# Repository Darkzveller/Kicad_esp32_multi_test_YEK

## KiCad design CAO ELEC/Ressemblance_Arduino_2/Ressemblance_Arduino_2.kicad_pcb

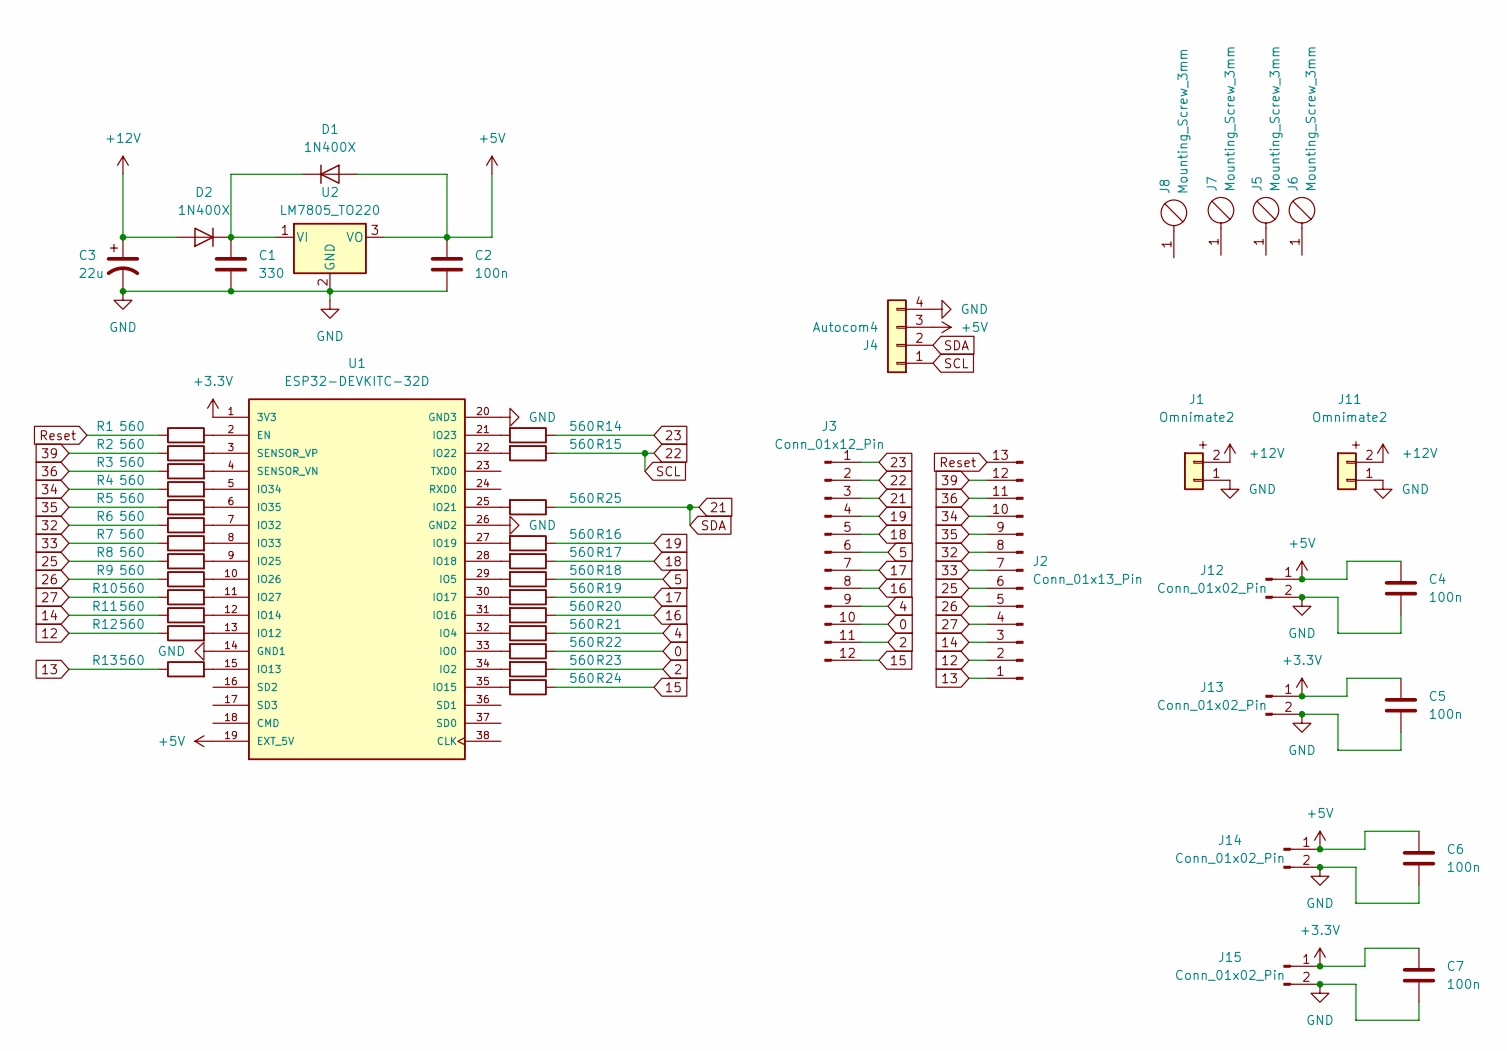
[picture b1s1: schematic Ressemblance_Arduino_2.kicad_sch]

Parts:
C1: 330; C_Rect_L7.0mm_W2.5mm_P5.00mm
C2, C4, C5, C6, C7: 100n; C_Rect_L7.0mm_W2.5mm_P5.00mm
C3: 22u; CP_Radial_D5.0mm_P2.50mm
D1, D2: 1N400X; D_DO-41_SOD81_P10.16mm_Horizontal
J1, J11: Omnimate2; OmnimateSL-5,08_1x02_P5.08mm_Vertical
J2: Conn_01x13_Pin; PinHeader_1x13_P2.54mm_Vertical
J3: Conn_01x12_Pin; PinHeader_1x12_P2.54mm_Vertical
J4: Autocom4; PinHeader_1x04_P2.00mm_Vertical
J5, J6, J7, J8: Mounting_Screw_3mm
J12, J13, J14, J15: Conn_01x02_Pin; PinHeader_1x02_P2.54mm_Vertical
R1, R2, R3, R4, R5, R6, R7, R8, R9, R10, R11, R12, R13, R14, R15, R16, R17, R18, R19, R20, R21, R22, R23, R24, R25: 560; R_Axial_DIN0207_L6.3mm_D2.5mm_P10.16mm_Horizontal
U1: ESP32-DEVKITC-32D; MODULE_ESP32-DEVKITC-32D; PARTREV 4
U2: LM7805_TO220; TO-220-3_Horizontal_TabDown

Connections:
0: J3.10, R22.1
2: J3.11, R23.1
4: J3.9, R21.1
5: J3.6, R18.1
12: J2.2, R12.1
13: J2.1, R13.1
14: J2.3, R11.1
15: J3.12, R24.1
16: J3.8, R20.1
17: J3.7, R19.1
18: J3.5, R17.1
19: J3.4, R16.1
21: J3.3, J4.2, R25.1
22: J3.2, J4.1, R15.1
23: J3.1, R14.1
25: J2.6, R8.1
26: J2.5, R9.1
27: J2.4, R10.1
32: J2.8, R6.1
33: J2.7, R7.1
34: J2.10, R4.1
35: J2.9, R5.1
36: J2.11, R3.1
39: J2.12, R2.1
+3.3V: C5.1, C7.1, J13.1, J15.1, U1.1 (3V3)
+5V: C2.1, C4.1, C6.1, D1.2 (A), J4.3, J12.1, J14.1, U1.19 (EXT_5V), U2.3 (VO)
+12V: C3.1, D2.2 (A), J1.2, J11.2
GND: C1.2, C2.2, C3.2, C4.2, C5.2, C6.2, C7.2, J1.1, J4.4, J11.1, J12.2, J13.2, J14.2, J15.2, U1.14 (GND1), U1.20 (GND3), U1.26 (GND2), U2.2 (GND)
unnamed: C1.1, D1.1 (K), D2.1 (K), U2.1 (VI)
unnamed: R1.2, U1.2 (EN)
unnamed: R22.2, U1.33 (IO0)
unnamed: R23.2, U1.34 (IO2)
unnamed: R21.2, U1.32 (IO4)
unnamed: R18.2, U1.29 (IO5)
unnamed: R12.2, U1.13 (IO12)
unnamed: R13.2, U1.15 (IO13)
unnamed: R11.2, U1.12 (IO14)
unnamed: R24.2, U1.35 (IO15)
unnamed: R20.2, U1.31 (IO16)
unnamed: R19.2, U1.30 (IO17)
unnamed: R17.2, U1.28 (IO18)
unnamed: R16.2, U1.27 (IO19)
unnamed: R25.2, U1.25 (IO21)
unnamed: R15.2, U1.22 (IO22)
unnamed: R14.2, U1.21 (IO23)
unnamed: R8.2, U1.9 (IO25)
unnamed: R9.2, U1.10 (IO26)
unnamed: R10.2, U1.11 (IO27)
unnamed: R6.2, U1.7 (IO32)
unnamed: R7.2, U1.8 (IO33)
unnamed: R4.2, U1.5 (IO34)
unnamed: R5.2, U1.6 (IO35)
unnamed: R3.2, U1.4 (SENSOR_VN)
unnamed: R2.2, U1.3 (SENSOR_VP)
Reset: J2.13, R1.1

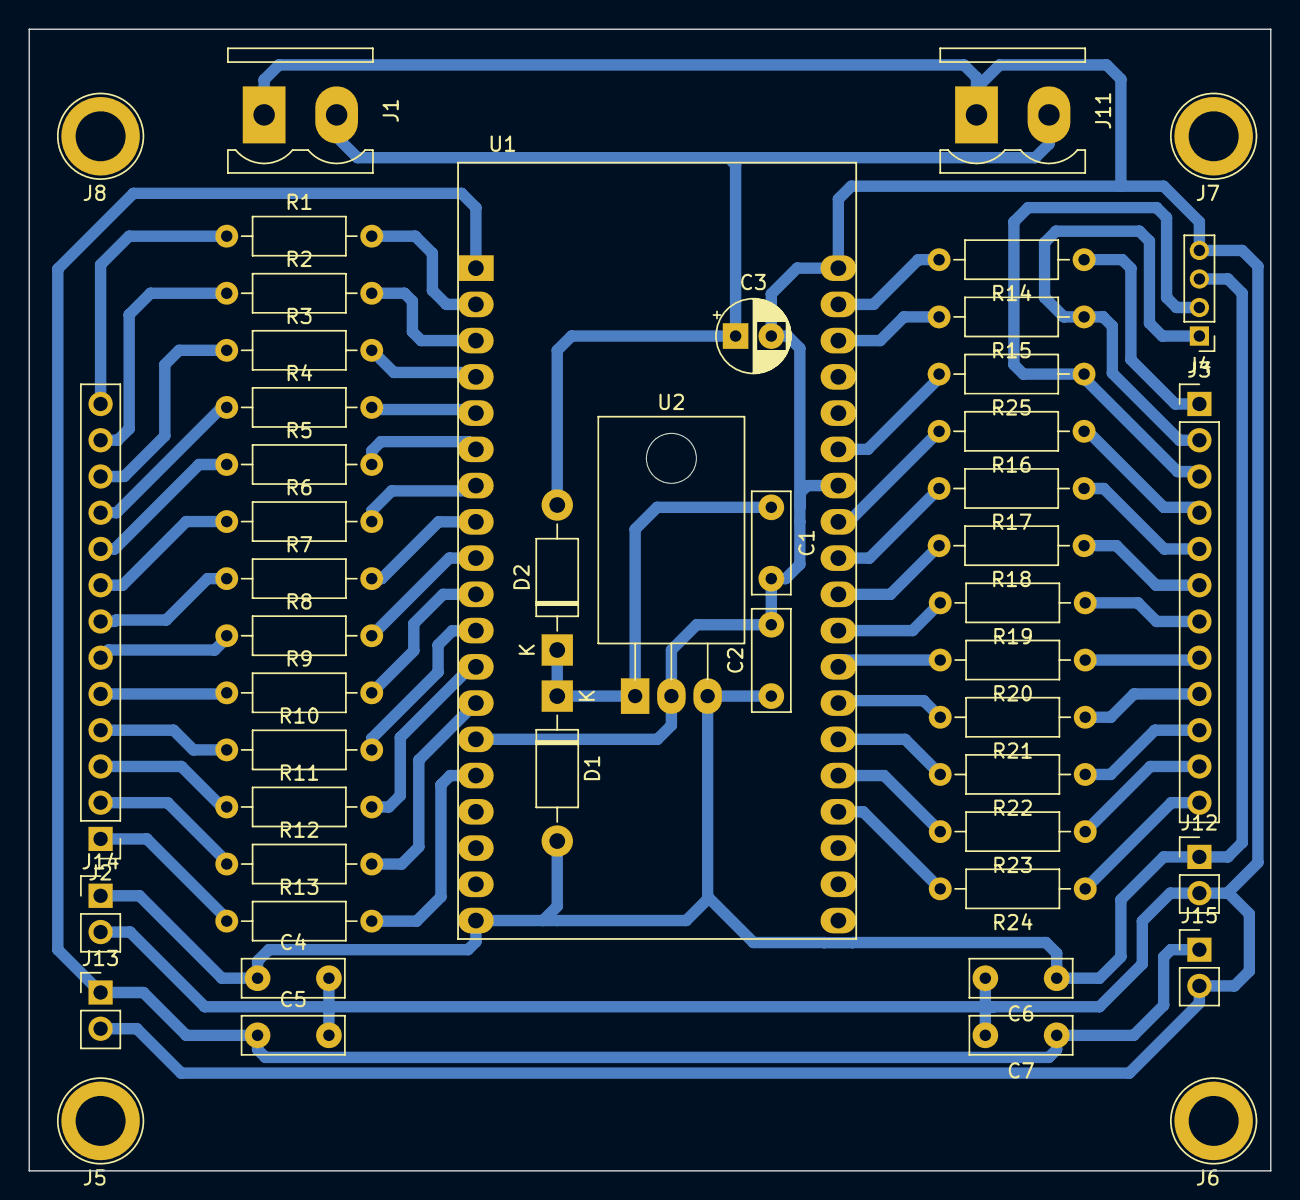
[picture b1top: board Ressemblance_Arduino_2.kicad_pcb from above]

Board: 2 copper layers, 87.0 x 80.0 mm, 49 parts (0 on the bottom side), 55 nets.

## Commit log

2025-06-22 Création du solidworks pour la boite pour eviter les court circuit
2025-06-22 J'ai rangé dans des dossiers pour s'y retrouvé
